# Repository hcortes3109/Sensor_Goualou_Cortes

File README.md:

# Sensor_Goualou_Cortes

# Sommaire

<!-- TOC depthFrom:2 -->
  - [1. Introduction](#1-Introduction)
  - [2. Code Arduino](#2-Code-Arduino)
  - [3. Kicad](#3-kicad)
  - [4. Application Android](#4-Application-Android)
  - [5. Resultats et datasheet](#5-Resultats-et-datasheet)
  - [6. Conclusion et pistes d'amelioration](#5-Conclusion-et-pistes-d'amelioration)
  - [7. Contact](#7-Contact)
<!-- /TOC -->

# 1. Introduction
Ce projet a été réalisé au cours de l'unité de formation "Du Capteur au Banc de Test" de la 4ème année du cursus “Génie Physique” à l’INSA de Toulouse.  L'objectif de ce dernier est de réaliser un capteur de déformation à base de graphite. 

Le graphite est un allotrope naturel de Carbone (comme le diamant), avec la propriété très  intéressante d’avoir une très bonne conductivité électrique.

Le capteur se base sur le fait que les électrons se déplacent entre les nanoparticules de graphite par effet tunnel. L’effet tunnel est un phénomène quantique, qui autorise certains objets quantiques (ici, ce sont les électrons), à franchir une barrière de potentiel alors que son énergie est inférieure à celle minimale pour franchir la barrière.
Lorsque nous exerçons une contrainte mécanique afin de plier le capteur, nous allons modifier la distance entre les nanoparticules du capteur, et ainsi modifier sa conductivité électrique, ce qui se traduit par une variation de résistance alors mesurable. Nous voulons utiliser cette propriété pour réaliser une jauge de contrainte avec plusieurs avantages, tels que peu onéreux ainsi que écoresponsable.

Nous allons donc colorier au crayon des capteurs sur une feuille de papier afin d'y laisser une fine couche de graphite. Nous avons la possibilité d’utiliser plusieurs types de crayons, qui se différencient par une variation de la concentration de graphite contenue dans ces derniers. Cette différence nous donnera en fonction de la déformation imposée plusieurs comportements de résistances.  

Afin de pouvoir relever la valeur de la résistance du capteur, nous avons conçu une shield avec un amplificateur transimpédance, un écran OLED, un encodeur rotatoire, ainsi qu'un module Bluetooth. Nous plaçons alors cette shield sur une carte Arduino UNO, programmée par un code Arduino.

Nous présentons ci-dessous les différentes étapes de l'élaboration de notre capteur :
- Code Arduino
- Design du shield
- Application android
- Résultat, Datasheet

# 2.Code Arduino
Nous avons réalisé un code Arduino fonctionnel, qui nous permet de contrôler un amplificateur transimpédance, un écran OLED ainsi qu’un module Bluetooth. Le code Arduino se trouve dans le dossier **“Main_Code”**.

Ce code assure plusieurs fonctions.
Il connaît les variables du circuit (résistance, tension d’entrée), et est capable de lire la tension de sortie du circuit, sur le pin digital A0. Alors nous sommes à même de calculer dans le code la valeur de la tension aux bornes de la résistance, et donc la valeur de la résistance du capteur.
Il assure également l’envoie de données sur l'application à l’aide du module bluetooth. Pour cela, il faut s’assurer que la carte arduino alimente le module,  et s'occupe de la communication des données.
L’affichage sur l’écran OLED de la valeur de la tension aux bornes du capteur et de la résistance est également géré par le code. Pour cela, nous avons dû télécharger des librairies Adafruit, puis gérer l’affichage des grandeurs physiques souhaitées sur l’écran.

Notons que ce code n’utilise pas l’encodeur rotatoire. En effet, lorsque nous agissons sur l’encodeur rotatoire de notre PCB, il y a un court circuit qui éteint nos appareils. Nous avons donc décidé de réaliser l’ensemble du dispositif en laissant l’encodeur rotatoire, mais sans l’utiliser.
De plus, la partie du code utilisant l’encodeur rotatoire est bien présente afin de réaliser un menu sur l’OLED. Mais le code n’est pas terminé, et demande encore quelques ajustements pour être fonctionnel.

# 3. KiCad
Nous avons utilisé le logiciel KiCad afin de réaliser la “shield”, qui nous permettra de mesurer la résistance de nos capteurs. Avec KiCad, nous sommes en mesure de simuler des circuits électroniques avant de lancer les impressions de notre PCB. 
Nous avons donc conçu un circuit électronique qui nous permet de mesurer en sortie du circuit une valeur de tension proportionnelle à la valeur de la résistance mesurée. Nous pouvons donc remonter à la résistance du capteur. Pour celà, nous y avons placé les composants ci-dessous : 

- écran OLED (affichage des valeurs de résistance et de tension mesurée)
- module Bluetooth (connexion entre Android et le PCB via l’APK)
- encodeur rotatoire (création d’un menu)
- amplificateur transimpédance

La tension aux bornes du capteur étant très faible, du fait que la résistance du capteur soit très grande, il nous faut rajouter un amplificateur transimpédance afin que la tension de sortie du circuit électronique soit assez grande et donc mesurable.
Notons que le gain de cet amplificateur dépend du rapport R3/R2, nous avons choisi ce rapport comme étant égal à 100, mais nous pourrions choisir une valeur différente si nous voulons modifier la plage de résistance à mesurer.

Une fois les tests réalisés, nous avons lancé l’impression de notre circuit via une photolithographie extrême ultraviolette (sous masque), puis après utilisation d’une solution dite de développement, nous avons procédé au perçage du PCB, permettant le soudage des composants.

Le détail de la schématique du circuit électronique est visible dans le dossier “Kicad”, où l’on présente la conception de l’ensemble du circuit électronique.

# 4. Application Android
L’idée de ce projet étant de mesurer la variation de résistance de nos capteurs en fonction de la concentration de Graphite, pour plus de confort et de lisibilité de nos mesures, nous avons réalisé une Application Android via le logiciel MIT App Inventor : http://ai2.appinventor.mit.edu . 
Celle-ci assure la connexion Bluetooth avec notre Shield, affiche la valeur de la tension et de la résistance mesurée en temps réel et trace également l’évolution de la résistance du capteur mesurée en fonction du temps. 

Vous pourrez trouver le code à insérer sur le site internet de MIT App Inventor dans le dossier “APK”.

# 5. Résultats, Datasheet

Nous avons créé plusieurs capteurs, en les "coloriant" avec divers types de crayons à papier (HB,B,...). Chaque capteur possède, avec le type de crayon en question, sa propre résistance avant et pendant la déformation. Nous avons pu avoir des résultats sur les crayons à papier B et HB.

Nous présentons sur le fichier “**curve.png**” deux courbes présentant la variation de la résistance du capteur en fonction de sa déformation pour un capteur avec un graphite B et un capteur avec un graphite HB.

Nous observons une petite tendance, les capteurs de type “HB” ont une résistance qui évoluent plus rapidement avec la déformation que les capteurs de type “B”.
Nous avons comparé cette tendance aux mêmes courbes réalisées dans l’article de recherche “**Pencil_Drawn_Strain_Gauges**” par un groupe de chercheurs, et nous avons observé cette même tendance pour les capteurs de type “B” et les capteurs de type “HB”.

Nous présentons les caractéristiques du capteur ainsi que du PCB sur la datasheet, que nous avons appelé “**Datasheet_Sensor**” dans le dossier Github.

# 6. Conclusion et Pistes d'amélioration

Après avoir finalisé les tests de notre capteur, nous avons remarqué quelques pistes d’amélioration.

Tout d’abord, il nous faudrait refaire un PCB avec un meilleur soudage pour que l’utilisation de l’encodeur rotatoire ne soit pas responsable d’un court circuit. 

Par ailleurs, le problème majeur de notre capteur est qu’il est à usage unique, car trop fragile. A chaque fois que nous testons un capteur, nous déformons sa résistance de base de manière irréversible. Il faudrait donc dessiner le graphite sur un matériau  qui peut se déformer de manière réversible, mais tout de même assez souple pour pouvoir le déformer.

De plus, nous avons constaté que le choix du gain de l'amplificateur transimpédance est très important pour nos données. Nous avons fait le choix de poser R3/R2 = 100, avec R3 = 100 kOhms, et R2 = 1 kOhm. En réalité, si nous modifions ce gain, nous pouvons observer des plages de résistance différentes. Nous avons observé une tendance expérimentale, plus la résistance est faible, plus la modification de résistance due à la courbure est observable. Ainsi, nous avons pensé à la possibilité de modifier R2 afin de modifier la plage de valeur de la résistance du capteur.
Les résistances que nous avons utilisé sont des résistances ¼ de Watt, il faudra donc faire attention à ne pas prendre des résistances trop faibles afin de ne pas les surchauffer. Nous proposons sur le tableau “**different_choices_of_resistor**” quatre valeurs différentes de résistance choisies pour R2, avec la valeur minimale du capteur que l’on pourrait mesurer, ainsi que la tension maximale que l’on peut lui appliquer.

La tension que voit la résistance R2 (100 Ohms) dans notre cas est de 5V, car c’est la valeur de tension d’entrée de notre circuit. Cette valeur est la même que la tension maximale que la résistance peut supporter. Donc nous nous sommes dit qu’il s’agirait sûrement de la meilleure valeur de R2 possible pour notre dispositif. En soudant une résistance de 500 Ohms pour R2, notre dispositif se verrait davantage optimisé.

Mais il faut retenir que le choix de la résistance aurait un impact sur la plage de valeurs de résistance que l’on peut mesurer avec notre dispositif.

# 7. Contact

Etudiants en 4ème année du Génie Physique de l'INSA de Toulouse

**Arthur Goualou** : goualou.etud@insa-toulouse.fr

**Hugo Cortes** : hcortes@etud.insa-toulouse.fr

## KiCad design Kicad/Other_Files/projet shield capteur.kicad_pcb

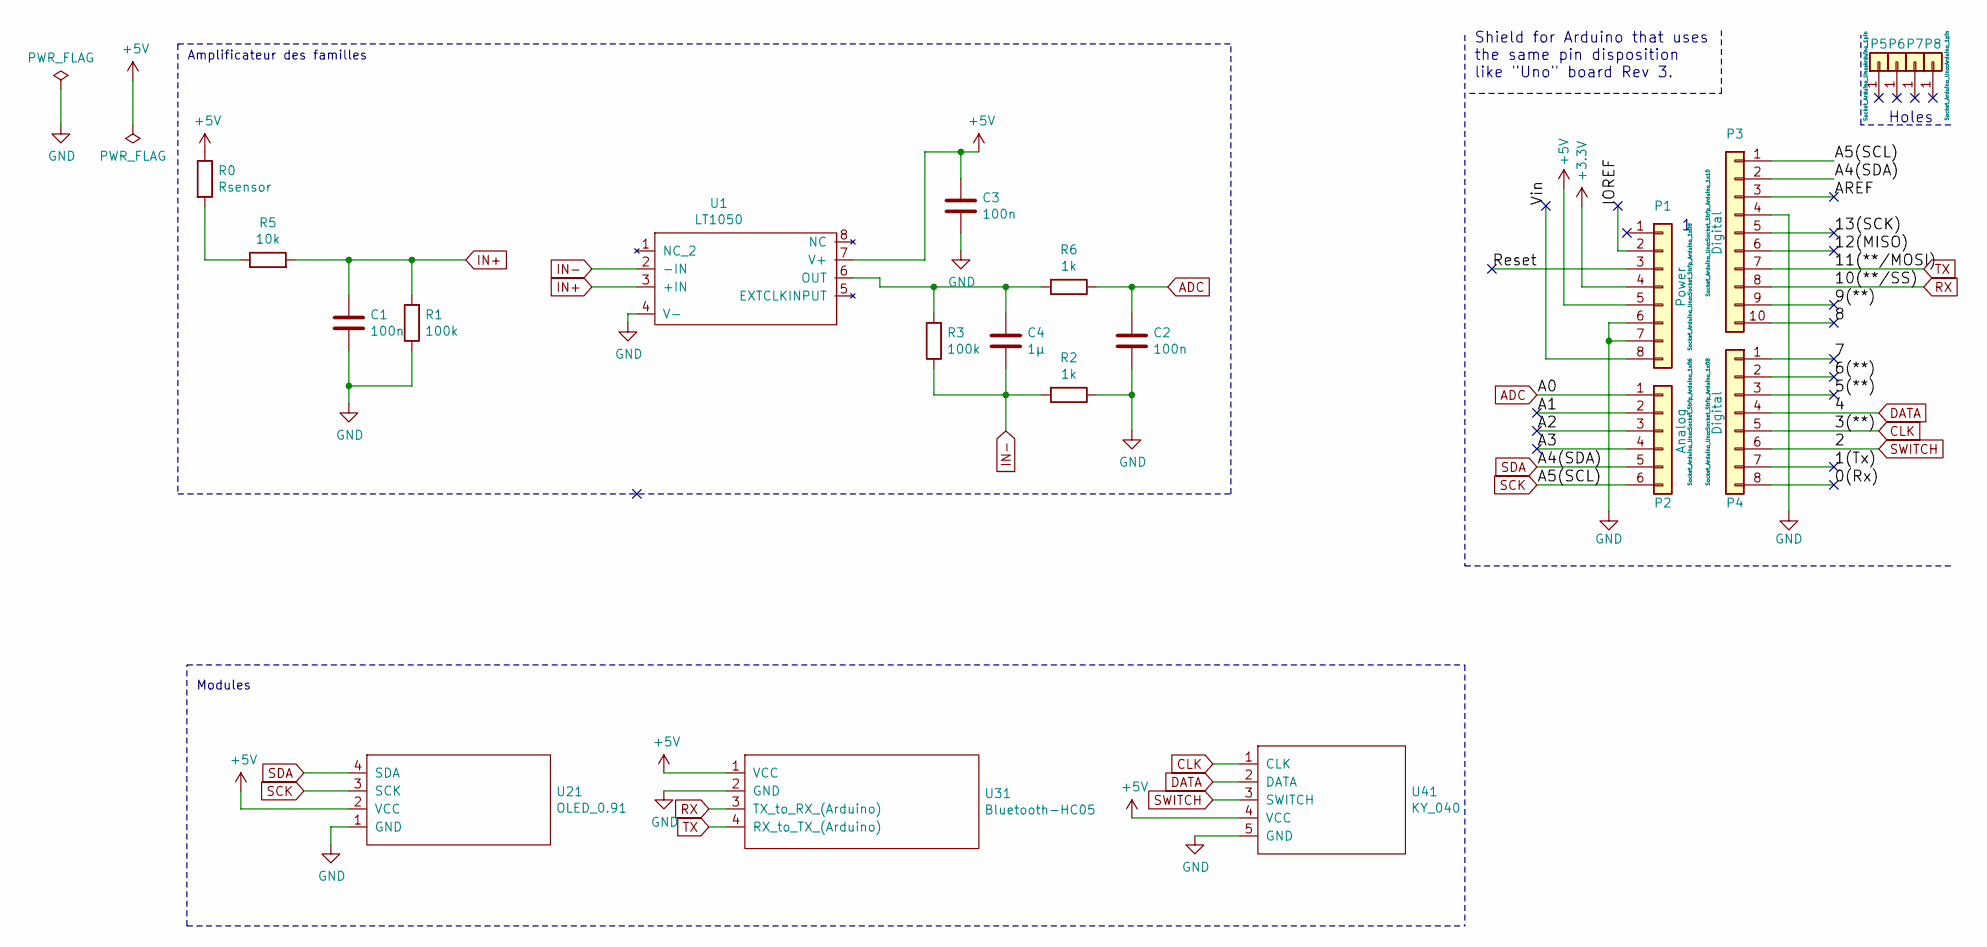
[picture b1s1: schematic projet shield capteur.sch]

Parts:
C1, C2, C3: 100n; C_Axial_L5.1mm_D3.1mm_P7.50mm_Horizontal
C4: 1µ; C_Axial_L5.1mm_D3.1mm_P7.50mm_Horizontal
P1: Power; Socket_Strip_Arduino_1x08
P2: Analog; Socket_Strip_Arduino_1x06
P3: Digital; Socket_Strip_Arduino_1x10
P4: Digital; Socket_Strip_Arduino_1x08
P5, P6, P7, P8: CONN_01X01; Arduino_1pin
R0: Rsensor; R_Axial_DIN0207_L6.3mm_D2.5mm_P10.16mm_Horizontal
R1, R3: 100k; R_Axial_DIN0207_L6.3mm_D2.5mm_P10.16mm_Horizontal
R2, R6: 1k; R_Axial_DIN0207_L6.3mm_D2.5mm_P10.16mm_Horizontal
R5: 10k; R_Axial_DIN0207_L6.3mm_D2.5mm_P10.16mm_Horizontal
U1: LT1050
U21: OLED_0.91; OLED
U31: Bluetooth-HC05; HC-05_BT
U41: KY_040; Encodeur

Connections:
+3V3: P1.4
+5V: C3.1, P1.5, R0.1, U1.7 (V+), U21.2 (VCC), U31.1 (VCC), U41.4 (VCC)
/0(Rx): P4.8
/1(Tx): P4.7
/5(**): P4.3
/6(**): P4.2
/7: P4.1
/8: P3.10
/9(**): P3.9
/12(MISO): P3.6
/13(SCK): P3.5
/A1: P2.2
/A2: P2.3
/A3: P2.4
/AREF: P3.3
/IOREF: P1.2
/Reset: P1.3
/Vin: P1.8
ADC: C2.1, P2.1, R6.1
CLK: P4.5, U41.1 (CLK)
DATA: P4.4, U41.2 (DATA)
GND: C1.2, C2.2, C3.2, P1.6, P1.7, P3.4, R1.1, R2.1, U1.4 (V-), U21.1 (GND), U31.2 (GND), U41.5 (GND)
IN+: C1.1, R1.2, R5.2, U1.3 (+IN)
IN-: C4.2, R2.2, R3.1, U1.2 (-IN)
unnamed: C4.1, R3.2, R6.2, U1.6 (OUT)
unnamed: R0.2, R5.1
RX: P3.8, U31.3 (TX_to_RX_(Arduino))
SCK: P2.6, P3.1, U21.3 (SCK)
SDA: P2.5, P3.2, U21.4 (SDA)
SWITCH: P4.6, U41.3 (SWITCH)
TX: P3.7, U31.4 (RX_to_TX_(Arduino))

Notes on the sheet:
Holes
Shield for Arduino that uses the same pin disposition like "Uno" board Rev 3.
Amplificateur des familles
Modules

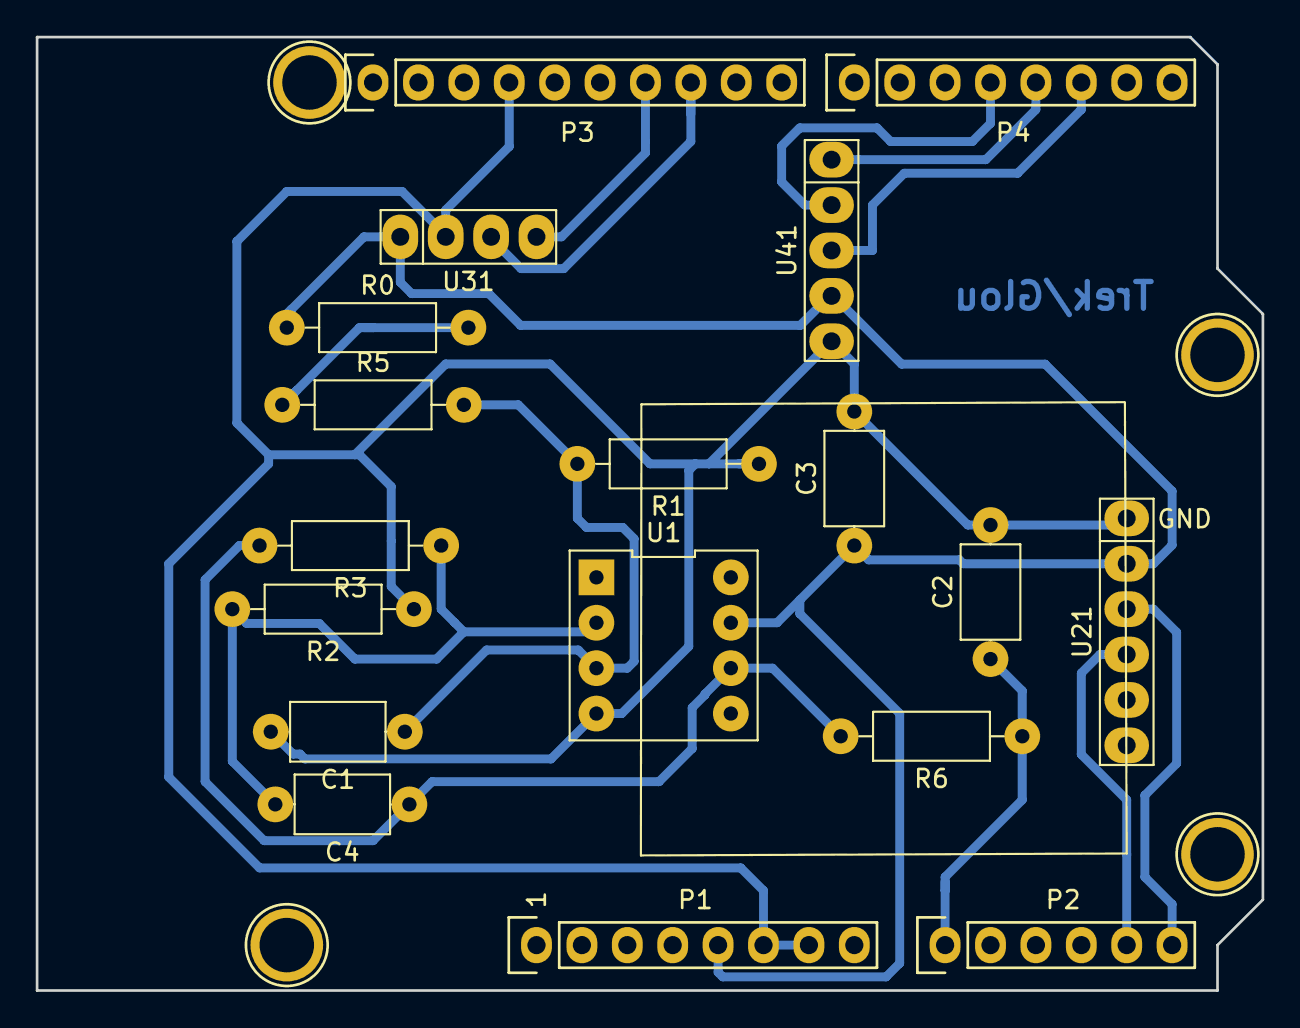
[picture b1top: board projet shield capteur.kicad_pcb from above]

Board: 2 copper layers, 68.6 x 53.3 mm, 22 parts (0 on the bottom side), 14 nets.

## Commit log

2021-01-28 version initiale du projet
2021-04-19 Create essai
2021-04-19 initial
2021-04-20 salut
2021-04-20 code
2021-04-21 modif
2021-04-22 schematic
2021-04-22 modificat
2021-04-22 application
2021-04-26 doc_update
2021-04-26 try2
2021-04-26 try3
2021-04-26 try4
2021-04-26 try5
2021-04-26 try6
2021-04-26 try7
2021-04-26 try8
2021-04-26 try9
2021-04-26 try10
2021-04-30 data
